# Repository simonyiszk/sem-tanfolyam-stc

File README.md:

# sem-tanfolyam-stc #

STC8G1K08 mikrovezérlős fejlesztőpanel a Schönherz Elektronikai Műhely alapozó tanfolyamához (2023-tól).
A projekt tartalmaz a devboardon kívül egy analóg hőmérővel, 7-szegmens kijelzőkkel, LED-ekkel, valamint gombokkal felszerelt alappanelt is, ezt tervezzük meg és készítjük el a tanfolyam során.

### Fejlesztőpanel fícsörök: ###
* Breadboard-ba illeszthető
* Feliratozott lábak
* USB-C csatlakozó
* Integrált programozó és táp-glitchelő áramkör
* Táp- és kommunikáció visszajelző LED-ek
* RESET gomb

[A mikrovezérlő adatlapja itt található.](https://www.stcmcudata.com/STC8F-DATASHEET/STC8G-EN.pdf)

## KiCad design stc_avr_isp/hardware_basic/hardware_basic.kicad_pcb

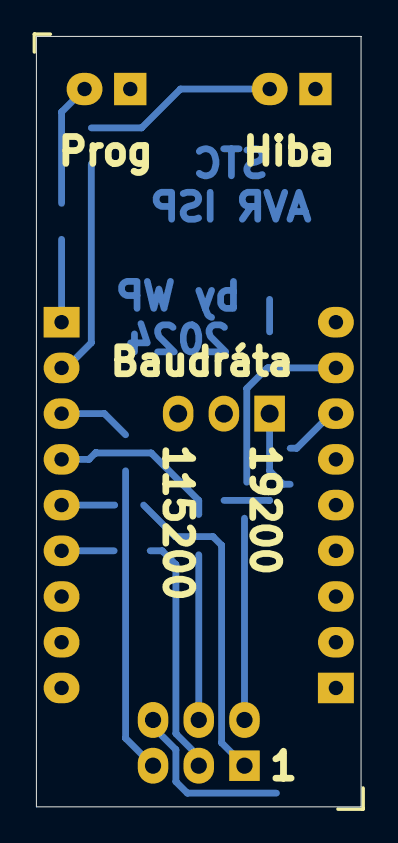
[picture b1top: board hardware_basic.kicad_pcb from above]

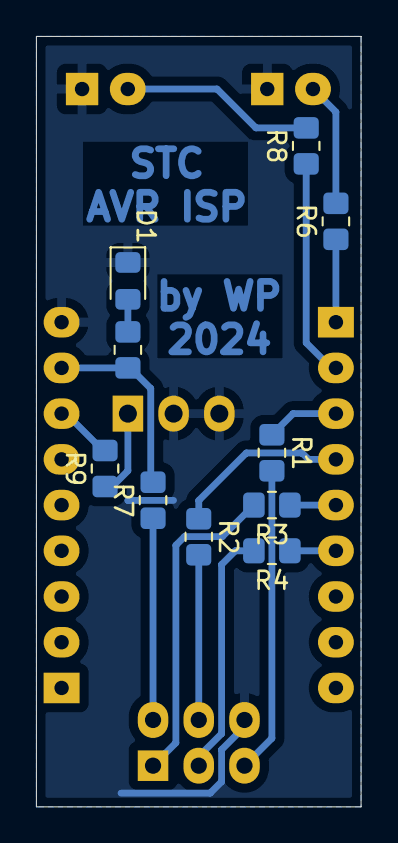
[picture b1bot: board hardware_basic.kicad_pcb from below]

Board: 2 copper layers, 18.0 x 42.8 mm, 16 parts (10 on the bottom side), 18 nets.

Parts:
D1: LED_Filled; LED_0805_2012Metric_Pad1.15x1.40mm_HandSolder
D2: PROG; LED_D3.0mm
D3: ERROR; LED_D3.0mm
J1, J2: Conn_01x09_Socket; PinSocket_1x09_P2.54mm_Vertical
J3: ISP; PinSocket_2x03_P2.54mm_Horizontal
J4: BAUD RATE; PinHeader_1x03_P2.54mm_Vertical
R1, R2, R3, R4: 100; R_0805_2012Metric_Pad1.20x1.40mm_HandSolder
R5, R6, R8, R9: 330; R_0805_2012Metric_Pad1.20x1.40mm_HandSolder
R7: 0; R_0805_2012Metric_Pad1.20x1.40mm_HandSolder

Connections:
+5V: J2.8, R5.1, R7.2
/MISO: J3.6, R3.2
/MOSI: J3.3, R2.2
/P1.0: J1.1, R6.1
/P1.1: J1.2, R8.1
/P5.5: J2.7, R9.2
/RESET: J3.2, R1.2
/SCLK: J3.4, R4.2
GND: D1.1 (K), D2.1 (K), D3.1 (K), J2.9, J3.1, J4.2, J4.3
unnamed: D1.2 (A), R5.2
unnamed: D2.2 (A), R6.2
unnamed: D3.2 (A), R8.2
unnamed: J1.3, R1.1
unnamed: J1.4, R2.1
unnamed: J1.5, R3.1
unnamed: J1.6, R4.1
unnamed: J3.5, R7.1
unnamed: J4.1, R9.1

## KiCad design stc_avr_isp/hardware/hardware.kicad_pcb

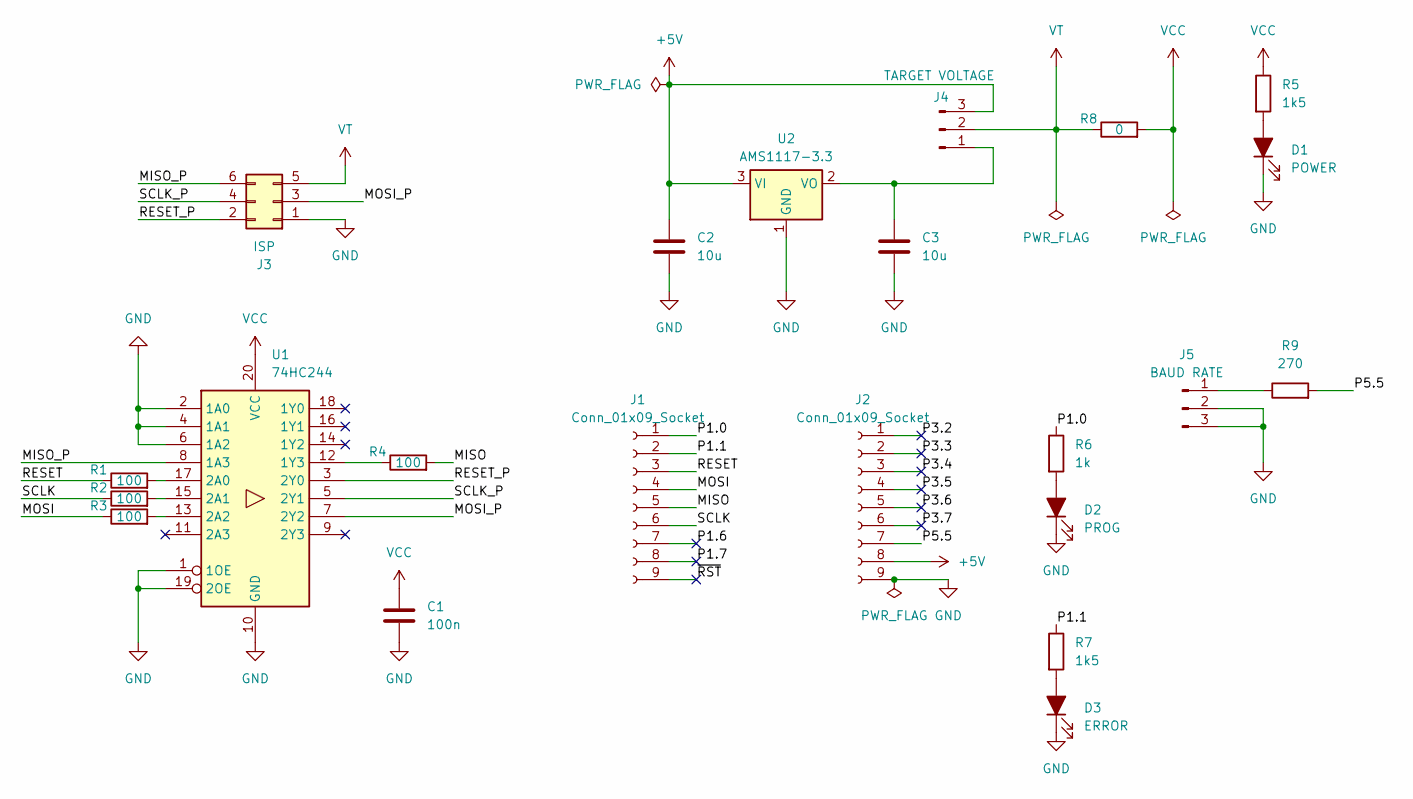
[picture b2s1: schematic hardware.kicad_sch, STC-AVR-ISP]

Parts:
C1: 100n; C_0805_2012Metric_Pad1.18x1.45mm_HandSolder
C2, C3: 10u; C_0805_2012Metric_Pad1.18x1.45mm_HandSolder
D1: POWER; LED_0805_2012Metric_Pad1.15x1.40mm_HandSolder
D2: PROG; LED_D3.0mm
D3: ERROR; LED_D3.0mm
J1, J2: Conn_01x09_Socket; PinSocket_1x09_P2.54mm_Vertical
J3: ISP; PinSocket_2x03_P2.54mm_Horizontal
J4: TARGET VOLTAGE; PinHeader_1x03_P2.54mm_Vertical
J5: BAUD RATE; PinHeader_1x03_P2.54mm_Vertical
R1, R2, R3, R4: 100; R_0805_2012Metric_Pad1.20x1.40mm_HandSolder
R5, R7: 1k5; R_0805_2012Metric_Pad1.20x1.40mm_HandSolder
R6: 1k; R_0805_2012Metric_Pad1.20x1.40mm_HandSolder
R8: 0; R_0805_2012Metric_Pad1.20x1.40mm_HandSolder
R9: 270; R_0805_2012Metric_Pad1.20x1.40mm_HandSolder
U1: 74HC244; TSSOP-20_4.4x6.5mm_P0.65mm
U2: AMS1117-3.3; SOT-223-3_TabPin2

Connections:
+5V: C2.1, J2.8, J4.3, U2.3 (VI)
/MISO: J1.5, R4.2
/MISO_P: J3.6, U1.8 (1A3)
/MOSI: J1.4, R3.1
/MOSI_P: J3.3, U1.7 (2Y2)
/P1.0: J1.1, R6.1
/P1.1: J1.2, R7.1
/P1.6: J1.7
/P1.7: J1.8
/P3.2: J2.1
/P3.3: J2.2
/P3.4: J2.3
/P3.5: J2.4
/P3.6: J2.5
/P3.7: J2.6
/P5.5: J2.7, R9.2
/RESET: J1.3, R1.1
/RESET_P: J3.2, U1.3 (2Y0)
/SCLK: J1.6, R2.1
/SCLK_P: J3.4, U1.5 (2Y1)
/~RST: J1.9
GND: C1.2, C2.2, C3.2, D1.1 (K), D2.1 (K), D3.1 (K), J2.9, J3.1, J5.2, J5.3, U1.1 (1OE), U1.2 (1A0), U1.4 (1A1), U1.6 (1A2), U1.10 (GND), U1.19 (2OE), U2.1 (GND)
unnamed: D1.2 (A), R5.2
unnamed: D2.2 (A), R6.2
unnamed: D3.2 (A), R7.2
unnamed: C3.1, J4.1, U2.2 (VO)
unnamed: J5.1, R9.1
unnamed: R4.1, U1.12 (1Y3)
unnamed: R1.2, U1.17 (2A0)
unnamed: R2.2, U1.15 (2A1)
unnamed: R3.2, U1.13 (2A2)
VCC: C1.1, R5.1, R8.2, U1.20 (VCC)
VT: J3.5, J4.2, R8.1

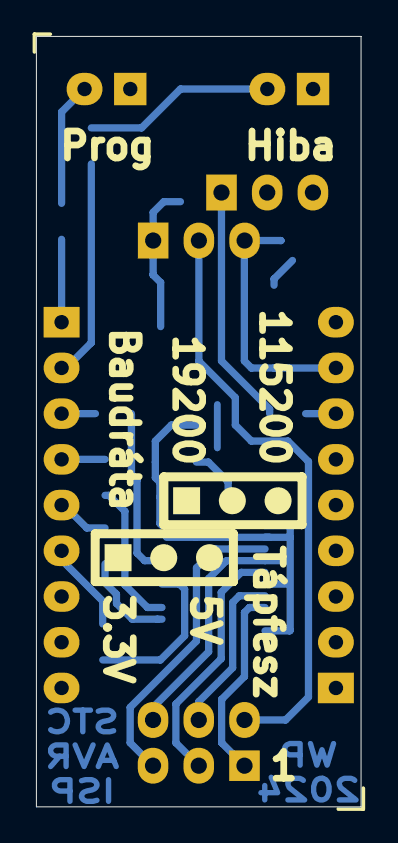
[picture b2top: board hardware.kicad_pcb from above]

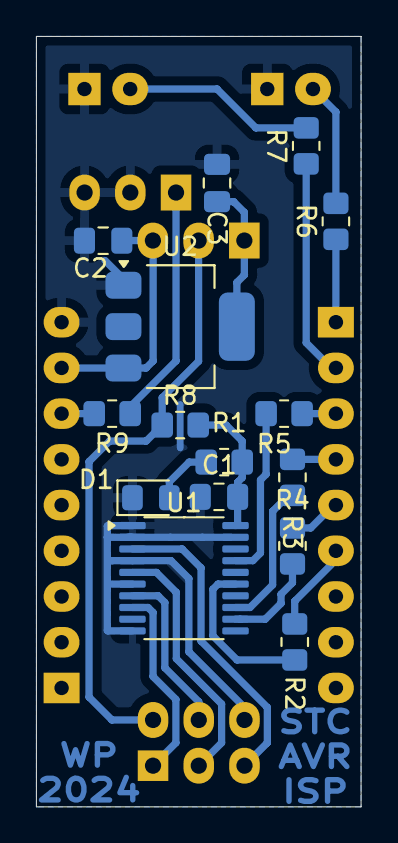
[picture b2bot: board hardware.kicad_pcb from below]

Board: 2 copper layers, 18.0 x 42.8 mm, 22 parts (15 on the bottom side), 24 nets.

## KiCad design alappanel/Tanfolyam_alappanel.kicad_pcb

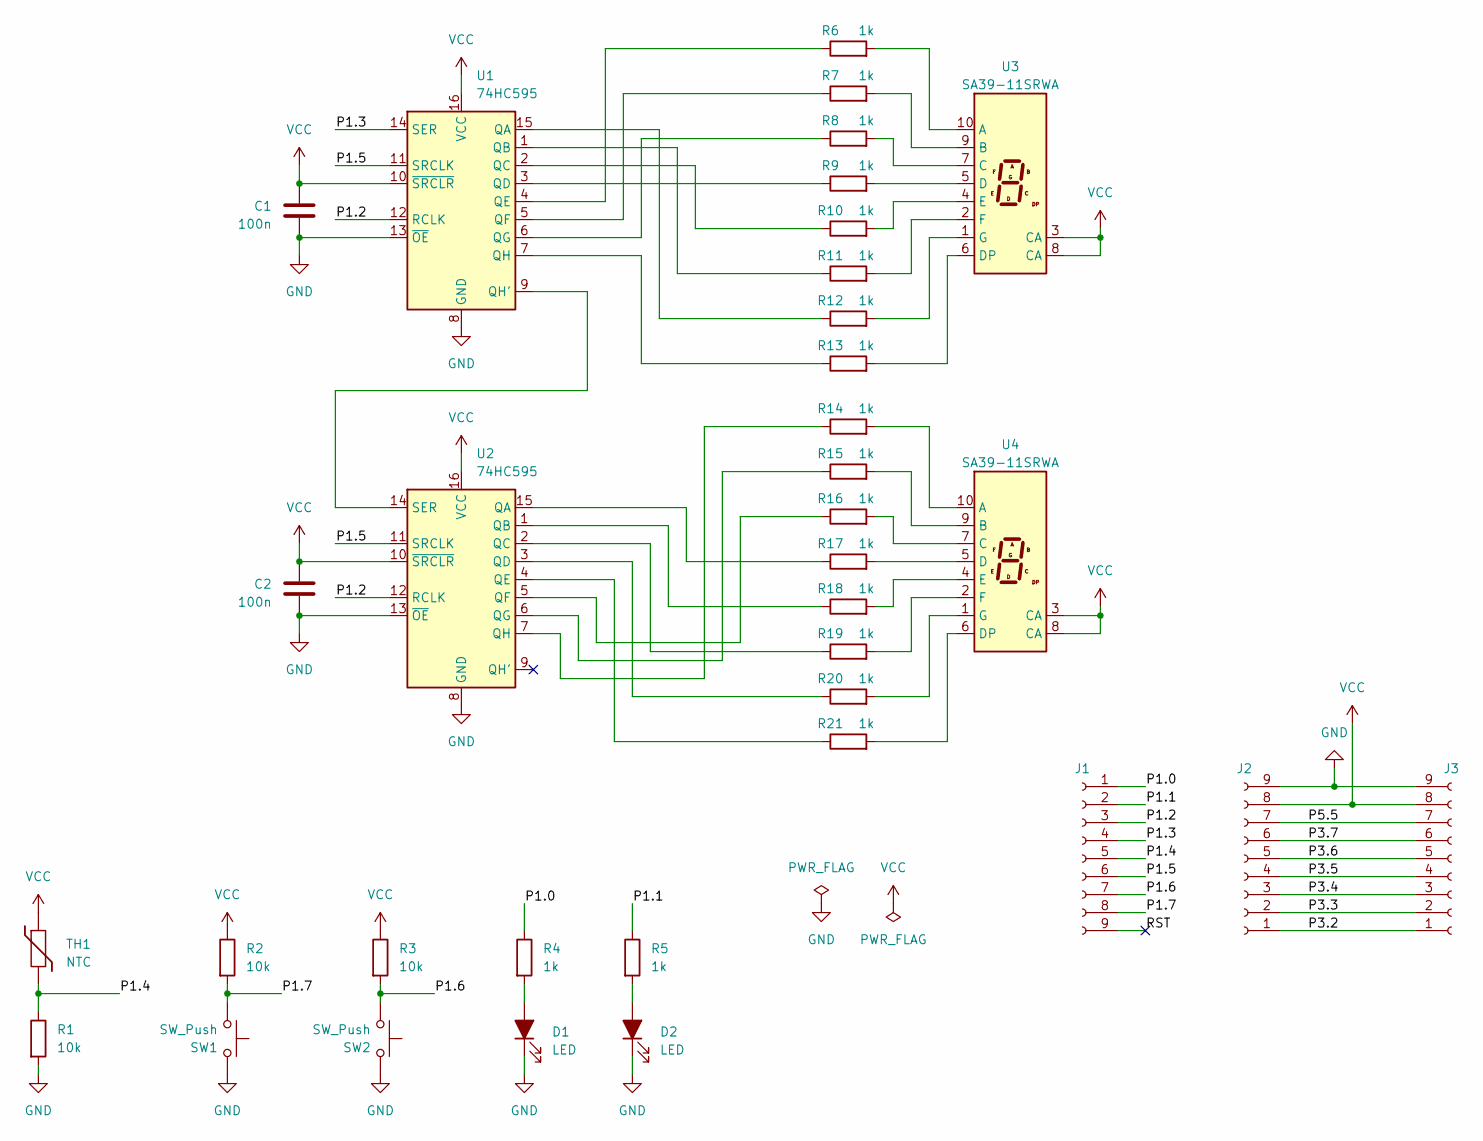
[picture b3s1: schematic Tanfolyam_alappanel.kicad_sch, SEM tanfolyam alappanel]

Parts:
C1, C2: 100n; C_1206_3216Metric_Pad1.33x1.80mm_HandSolder
D1, D2: LED; LED_D5.0mm
J1, J2: Connector; PinSocket_1x09_P2.54mm_Vertical
J3: Connector; PinHeader_1x09_P2.54mm_Vertical
R1, R2, R3: 10k; R_1206_3216Metric_Pad1.30x1.75mm_HandSolder
R4, R5, R6, R7, R8, R9, R10, R11, R12, R13, R14, R15, R16, R17, R18, R19, R20, R21: 1k; R_1206_3216Metric_Pad1.30x1.75mm_HandSolder
SW1, SW2: SW_Push; SW_PUSH_6mm
TH1: NTC; PinHeader_1x02_P2.54mm_Vertical
U1, U2: 74HC595; SOIC-16_3.9x9.9mm_P1.27mm
U3, U4: SA39-11SRWA; Sx39-1xxxxx

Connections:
/P1.0: J1.1, R4.1
/P1.1: J1.2, R5.1
/P1.2: J1.3, U1.12 (RCLK), U2.12 (RCLK)
/P1.3: J1.4, U1.14 (SER)
/P1.4: J1.5, R1.1, TH1.2
/P1.5: J1.6, U1.11 (SRCLK), U2.11 (SRCLK)
/P1.6: J1.7, R3.2, SW2.1
/P1.7: J1.8, R2.2, SW1.1
/P3.2: J2.1, J3.1
/P3.3: J2.2, J3.2
/P3.4: J2.3, J3.3
/P3.5: J2.4, J3.4
/P3.6: J2.5, J3.5
/P3.7: J2.6, J3.6
/P5.5: J2.7, J3.7
/RST: J1.9
GND: C1.2, C2.2, D1.1 (K), D2.1 (K), J2.9, J3.9, R1.2, SW1.2, SW2.2, U1.8 (GND), U1.13 (~OE), U2.8 (GND), U2.13 (~OE)
unnamed: D1.2 (A), R4.2
unnamed: D2.2 (A), R5.2
unnamed: R12.1, U1.15 (QA)
unnamed: R11.1, U1.1 (QB)
unnamed: R10.1, U1.2 (QC)
unnamed: R9.1, U1.3 (QD)
unnamed: R6.1, U1.4 (QE)
unnamed: R7.1, U1.5 (QF)
unnamed: R8.1, U1.6 (QG)
unnamed: U1.9 (QH'), U2.14 (SER)
unnamed: R13.1, U1.7 (QH)
unnamed: R17.1, U2.15 (QA)
unnamed: R18.1, U2.1 (QB)
unnamed: R19.1, U2.2 (QC)
unnamed: R20.1, U2.3 (QD)
unnamed: R21.1, U2.4 (QE)
unnamed: R16.1, U2.5 (QF)
unnamed: R15.1, U2.6 (QG)
unnamed: R14.1, U2.7 (QH)
unnamed: R6.2, U3.10 (A)
unnamed: R7.2, U3.9 (B)
unnamed: R8.2, U3.7 (C)
unnamed: R9.2, U3.5 (D)
unnamed: R13.2, U3.6 (DP)
unnamed: R10.2, U3.4 (E)
unnamed: R11.2, U3.2 (F)
unnamed: R12.2, U3.1 (G)
unnamed: R14.2, U4.10 (A)
unnamed: R15.2, U4.9 (B)
unnamed: R16.2, U4.7 (C)
unnamed: R17.2, U4.5 (D)
unnamed: R21.2, U4.6 (DP)
unnamed: R18.2, U4.4 (E)
unnamed: R19.2, U4.2 (F)
unnamed: R20.2, U4.1 (G)
VCC: C1.1, C2.1, J2.8, J3.8, R2.1, R3.1, TH1.1, U1.10 (~SRCLR), U1.16 (VCC), U2.10 (~SRCLR), U2.16 (VCC), U3.3 (CA), U3.8 (CA), U4.3 (CA), U4.8 (CA)

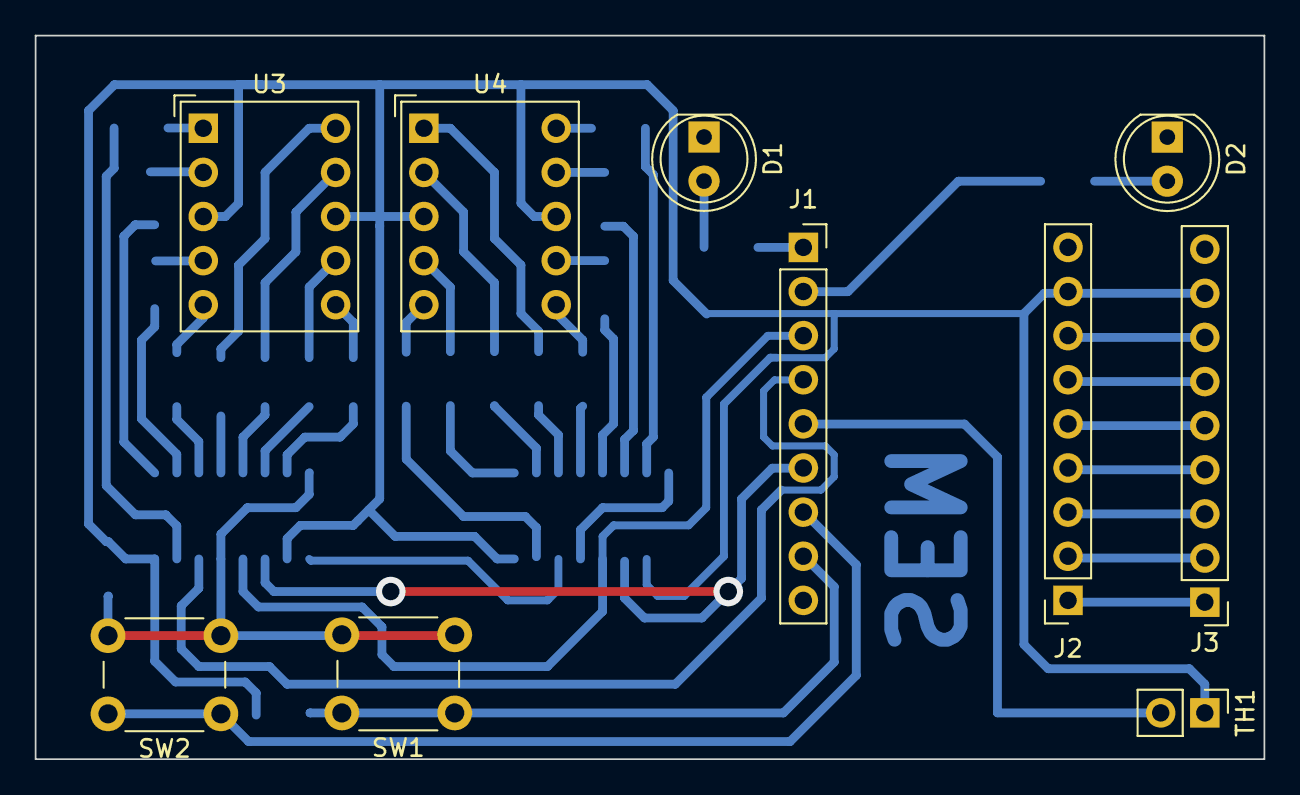
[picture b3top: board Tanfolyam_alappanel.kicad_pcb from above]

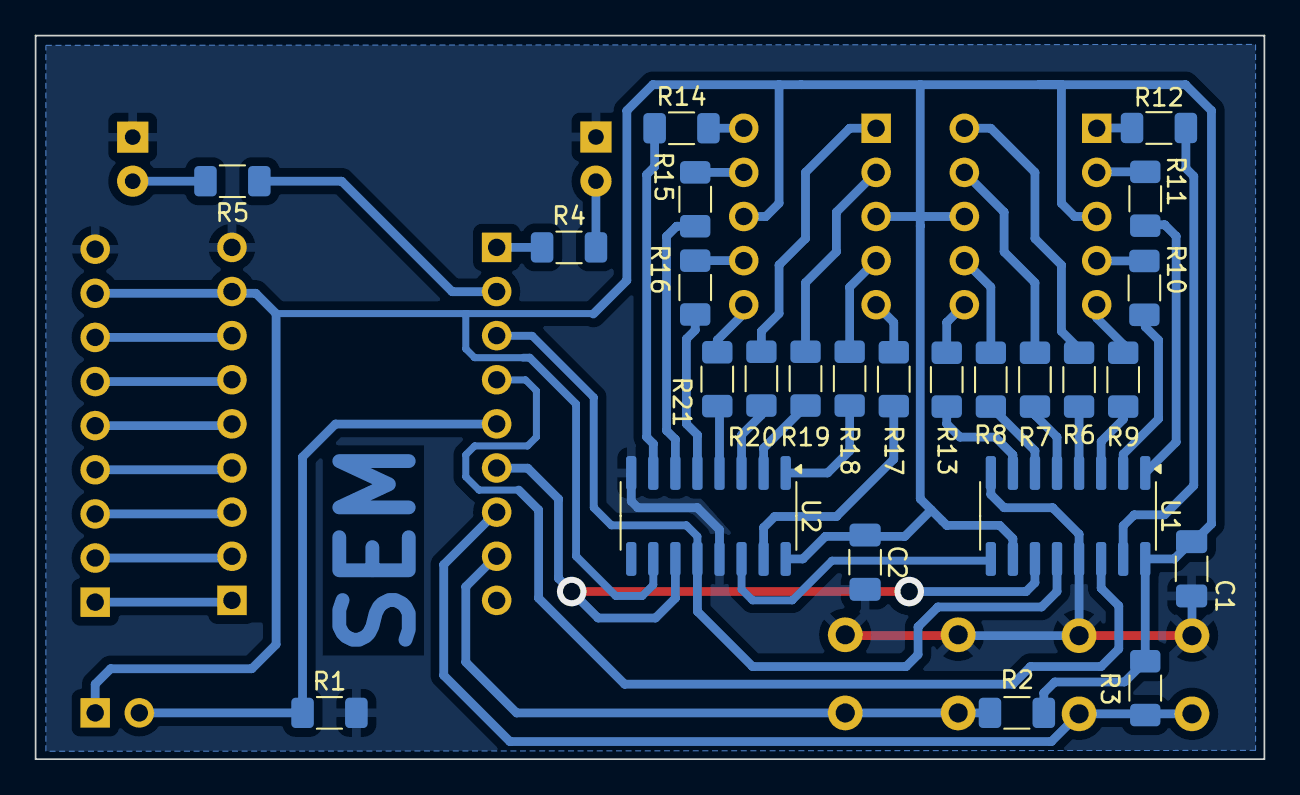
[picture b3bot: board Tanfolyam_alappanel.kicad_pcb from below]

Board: 2 copper layers, 70.7 x 41.7 mm, 35 parts (25 on the bottom side), 52 nets.

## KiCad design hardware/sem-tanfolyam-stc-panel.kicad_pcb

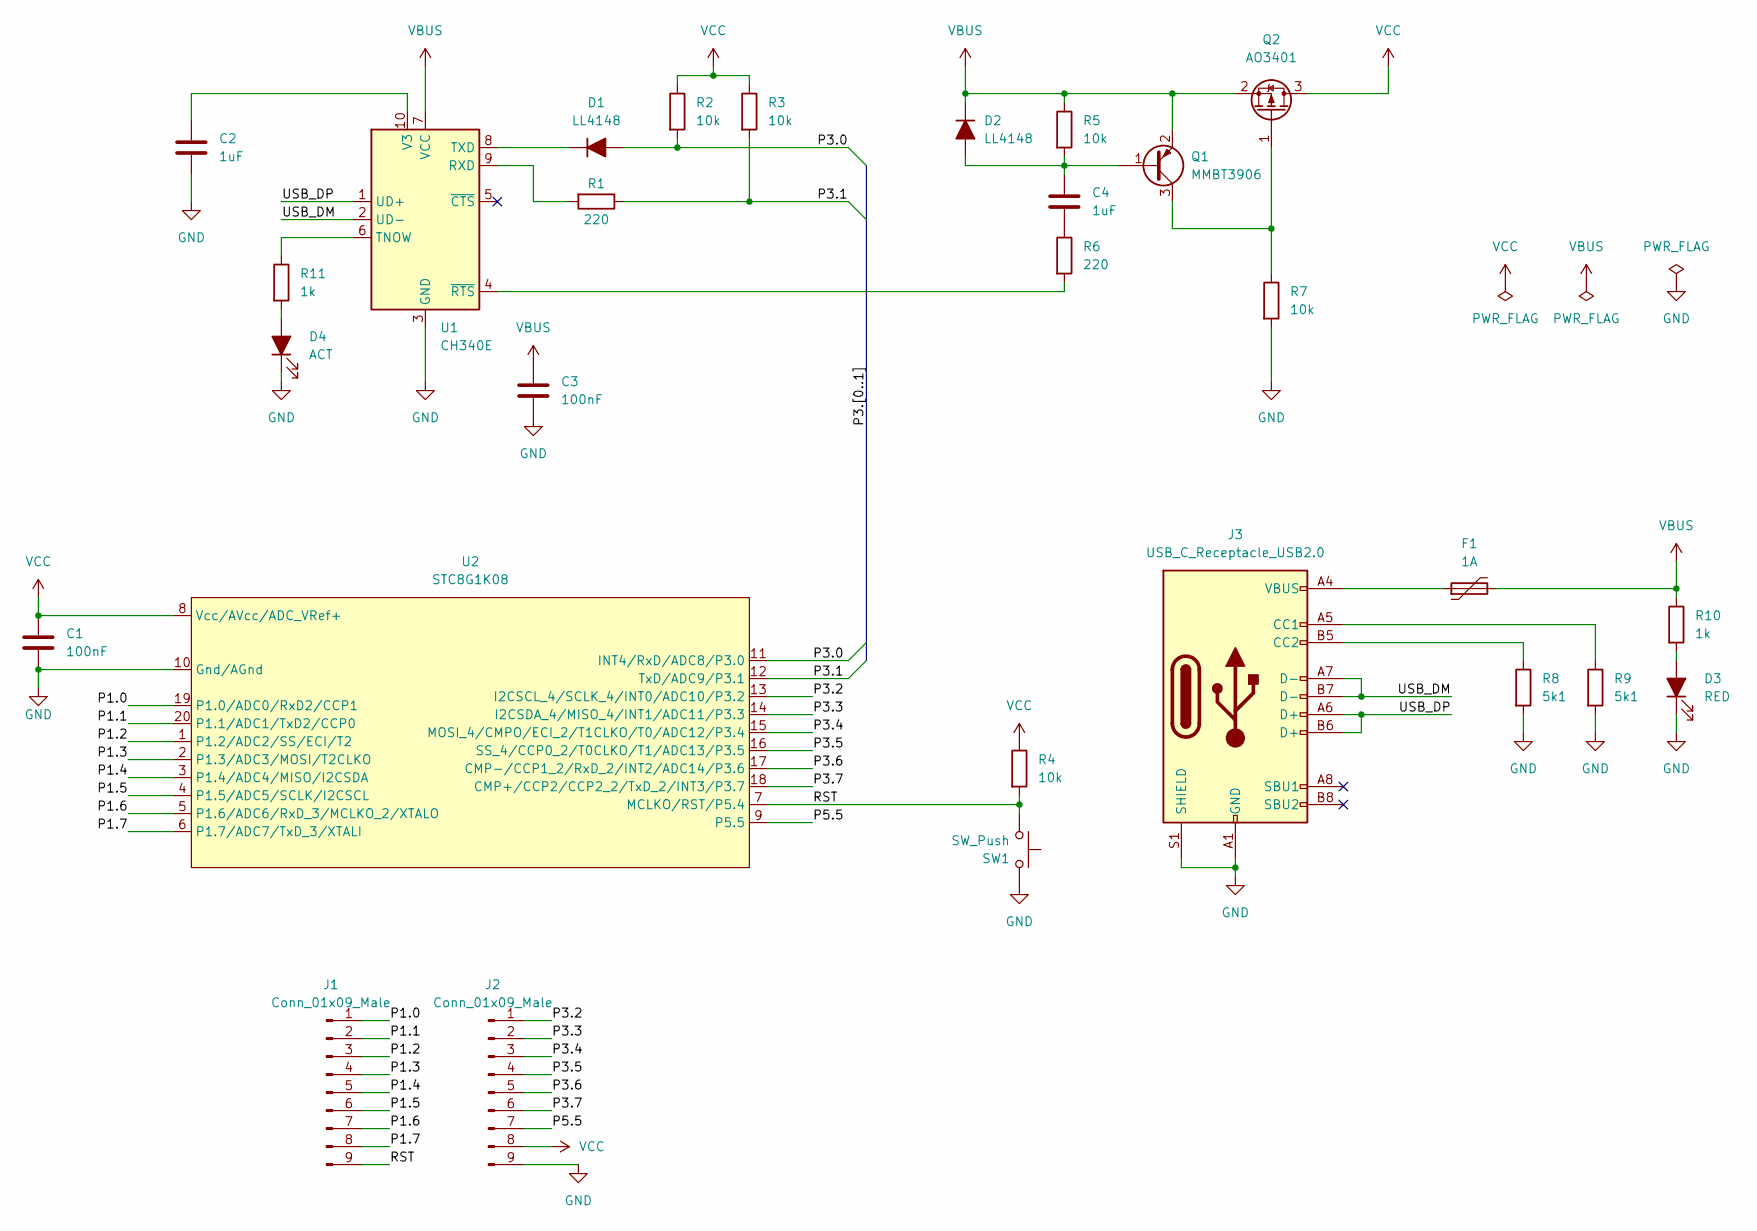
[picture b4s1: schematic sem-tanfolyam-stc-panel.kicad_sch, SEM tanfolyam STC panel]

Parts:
C1, C3: 100nF; C_0603_1608Metric
C2, C4: 1uF; C_0603_1608Metric
D1, D2: LL4148; D_MiniMELF
D3: RED; LED_0603_1608Metric
D4: ACT; LED_0603_1608Metric
F1: 1A; Fuse_1206_3216Metric
J1, J2: Conn_01x09_Male; PinHeader_1x09_P2.54mm_Vertical
J3: USB_C_Receptacle_USB2.0; USB_C_Receptacle_G-Switch_GT-USB-7010ASV
Q1: MMBT3906; SOT-23
Q2: AO3401; SOT-23
R1, R6: 220; R_0603_1608Metric
R2, R3, R4, R5, R7: 10k; R_0603_1608Metric
R8, R9: 5k1; R_0603_1608Metric
R10, R11: 1k; R_0603_1608Metric
SW1: SW_Push; SW_SPST_TL3342
U1: CH340E; MSOP-10_3x3mm_P0.5mm
U2: STC8G1K08; TSSOP-20_4.4x6.5mm_P0.65mm

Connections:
/P1.0: J1.1, U2.19 (P1.0/ADC0/RxD2/CCP1)
/P1.1: J1.2, U2.20 (P1.1/ADC1/TxD2/CCP0)
/P1.2: J1.3, U2.1 (P1.2/ADC2/SS/ECI/T2)
/P1.3: J1.4, U2.2 (P1.3/ADC3/MOSI/T2CLKO)
/P1.4: J1.5, U2.3 (P1.4/ADC4/MISO/I2CSDA)
/P1.5: J1.6, U2.4 (P1.5/ADC5/SCLK/I2CSCL)
/P1.6: J1.7, U2.5 (P1.6/ADC6/RxD_3/MCLKO_2/XTALO)
/P1.7: J1.8, U2.6 (P1.7/ADC7/TxD_3/XTALI)
/P3.0: D1.2 (A), R2.2, U2.11 (INT4/RxD/ADC8/P3.0)
/P3.1: R1.1, R3.2, U2.12 (TxD/ADC9/P3.1)
/P3.2: J2.1, U2.13 (I2CSCL_4/SCLK_4/INT0/ADC10/P3.2)
/P3.3: J2.2, U2.14 (I2CSDA_4/MISO_4/INT1/ADC11/P3.3)
/P3.4: J2.3, U2.15 (MOSI_4/CMPO/ECI_2/T1CLKO/T0/ADC12/P3.4)
/P3.5: J2.4, U2.16 (SS_4/CCP0_2/T0CLKO/T1/ADC13/P3.5)
/P3.6: J2.5, U2.17 (CMP-/CCP1_2/RxD_2/INT2/ADC14/P3.6)
/P3.7: J2.6, U2.18 (CMP+/CCP2/CCP2_2/TxD_2/INT3/P3.7)
/P5.5: J2.7, U2.9 (P5.5)
/RST: J1.9, R4.2, SW1.1, U2.7 (MCLKO/RST/P5.4)
/USB_DM: J3.A7 (D-), J3.B7 (D-), U1.2 (UD-)
/USB_DP: J3.A6 (D+), J3.B6 (D+), U1.1 (UD+)
GND: C1.2, C2.2, C3.2, D3.1 (K), D4.1 (K), J2.9, J3.A1 (GND), J3.A12 (GND), J3.B1 (GND), J3.B12 (GND), J3.S1 (SHIELD), R7.2, R8.2, R9.2, SW1.2, U1.3 (GND), U2.10 (Gnd/AGnd)
unnamed: C4.2, R6.1
unnamed: D1.1 (K), U1.8 (TXD)
unnamed: C4.1, D2.2 (A), Q1.1 (B), R5.2
unnamed: D3.2 (A), R10.2
unnamed: D4.2 (A), R11.2
unnamed: F1.1, J3.A4 (VBUS), J3.A9 (VBUS), J3.B4 (VBUS), J3.B9 (VBUS)
unnamed: J3.A5 (CC1), R9.1
unnamed: J3.B5 (CC2), R8.1
unnamed: Q1.3 (C), Q2.1 (G), R7.1
unnamed: R1.2, U1.9 (RXD)
unnamed: R11.1, U1.6 (TNOW)
unnamed: C2.1, U1.10 (V3)
unnamed: R6.2, U1.4 (~RTS)
VBUS: C3.1, D2.1 (K), F1.2, Q1.2 (E), Q2.2 (S), R5.1, R10.1, U1.7 (VCC)
VCC: C1.1, J2.8, Q2.3 (D), R2.1, R3.1, R4.1, U2.8 (Vcc/AVcc/ADC_VRef+)

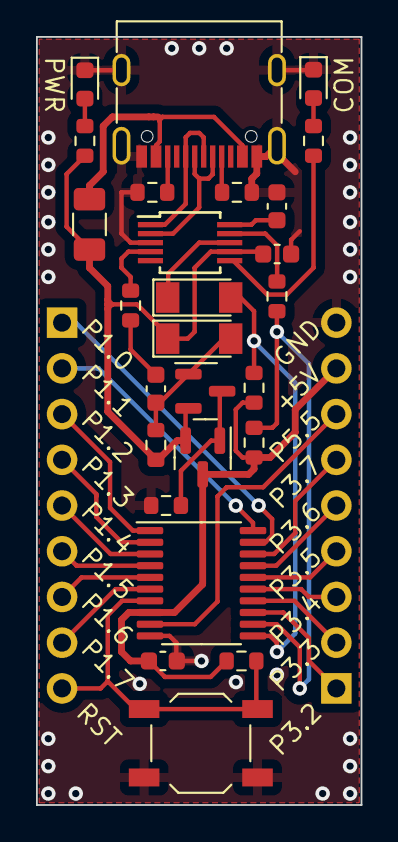
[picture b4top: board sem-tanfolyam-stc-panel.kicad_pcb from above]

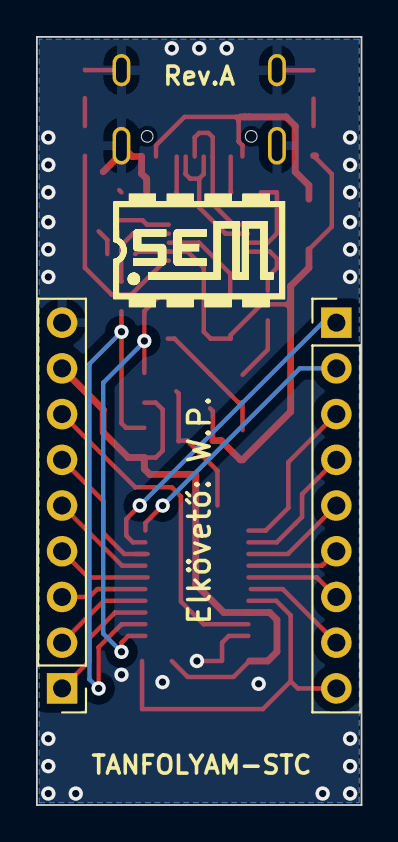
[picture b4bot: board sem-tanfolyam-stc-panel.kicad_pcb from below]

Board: 2 copper layers, 18.0 x 42.7 mm, 28 parts (2 on the bottom side), 36 nets.

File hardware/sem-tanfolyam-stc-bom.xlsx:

Comment | Designator | Footprint | JLCPCB Part #（optional）
100nF | C1, C3 | Capacitor_SMD:C_0603_1608Metric | C14663
1uF | C2, C4 | Capacitor_SMD:C_0603_1608Metric | C15849
LL4148 | D1, D2 | Diode_SMD:D_MiniMELF | C9808
Red | D3 | LED_SMD:LED_0603_1608Metric | C2286
Yellow | D4 | LED_SMD:LED_0603_1608Metric | C72038
1A | F1 | Fuse:Fuse_1206_3216Metric | C883131
Conn_01x09_Male | J1, J2 | Connector_PinHeader_2.54mm:PinHeader_1x09_P2.54mm_Vertical
USB_C_Receptacle_USB2.0 | J3 | Connector_USB:USB_C_Receptacle_G-Switch_GT-USB-7010ASV | C2765186
MMBT5401 | Q1 | Package_TO_SOT_SMD:SOT-23 | C8326
AO3401 | Q2 | Package_TO_SOT_SMD:SOT-23 | C15127
220 | R1, R6 | Resistor_SMD:R_0603_1608Metric | C8218
10k | R2, R3, R4, R5, R7 | Resistor_SMD:R_0603_1608Metric | C25804
5k1 | R8, R9 | Resistor_SMD:R_0603_1608Metric | C23186
1k | R10, R11 | Resistor_SMD:R_0603_1608Metric | C21190
SW_Push | SW1 | Button_Switch_SMD:SW_Push_1P1T_NO_6x6mm_H9.5mm | C318884
CH340E | U1 | Package_SO:MSOP-10_3x3mm_P0.5mm | C99652
STC8G1K08 | U2 | Package_SO:TSSOP-20_4.4x6.5mm_P0.65mm | C521757

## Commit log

2023-02-08 Add core schematic (Rev A.1) and STC8G1K08 symbol
2023-02-10 Add peripherals to schematic and 7-segment display symbol and footprint
2023-02-23 Add PCB design
2023-02-23 Remove USER LED from schematic
2023-02-25 BOM hozzáadva + hiányosságok meggyógyítva.
2023-02-25 Összemontírozva, gyártásra készen.
2023-02-26 Final touches, PANELIZATION NEEDED
2023-02-26 Panelizálva és megrendelve.
2023-02-27 Alappanel kapcsolási rajz hozzáadva
2023-03-23 Add single sided base board
2023-03-25 Changed 0805 footprints to 1206
2023-03-25 Gyártva a SEM-ben.
2023-04-02 Hőmérő teszt program.
2023-04-04 Apró módosítások.
2024-02-21 Újfajta szoftvertelepítési útmutató
2024-02-25 Add 7-segment display 3D model and tutorial (demo) project for kicad8
2024-02-25 Demo projekt
2024-03-07 Add interactive BOM
2024-03-07 Add Interactive BOM with references placed correctly on silkscreen layer
2024-03-07 Interaktív BOM, már a FAB rétegek feliratai is jó helyen vannak
2024-03-22 Add recent bug fixes in .platformio.ini config and update the pdf manual
2024-03-30 Add AVR-ISP baseboard design with working firmware
2024-04-06 Add fancy blink animation on reset, specify resistor values
